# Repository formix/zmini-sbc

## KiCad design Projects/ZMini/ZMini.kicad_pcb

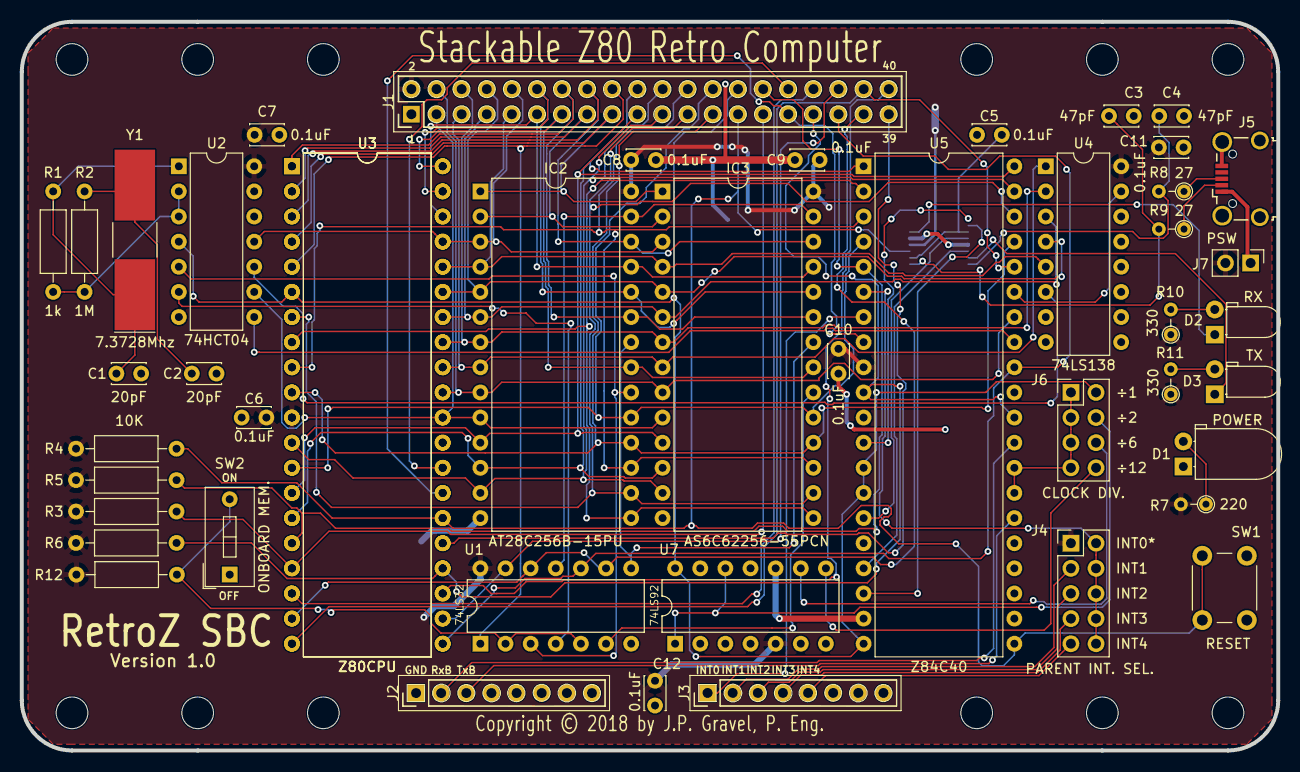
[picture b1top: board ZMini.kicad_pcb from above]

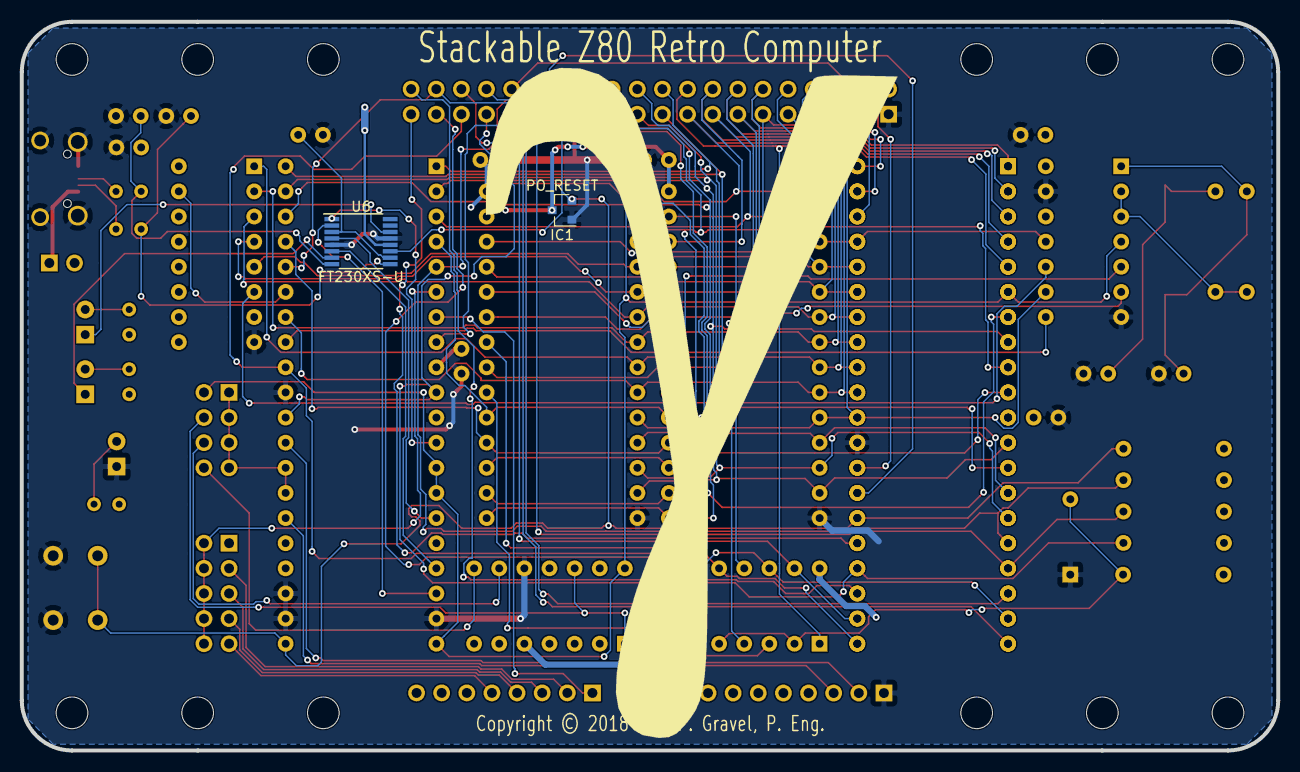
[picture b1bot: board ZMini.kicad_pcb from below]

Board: 2 copper layers, 127.0 x 73.7 mm, 60 parts (2 on the bottom side), 79 nets.

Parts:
C1, C2: 20pF; C_Disc_D3.4mm_W2.1mm_P2.50mm
C3, C4: 47pF; C_Disc_D3.4mm_W2.1mm_P2.50mm
C5, C6, C7, C8, C9, C10, C11, C12: 0.1uF; C_Disc_D3.4mm_W2.1mm_P2.50mm
D1: POWER; LED_D5.0mm_Horizontal_O1.27mm_Z3.0mm
D2: RX; LED_D3.0mm_Horizontal_O1.27mm_Z2.0mm
D3: TX; LED_D3.0mm_Horizontal_O1.27mm_Z2.0mm
H1, H2, H3, H4, H5, H6, H7, H8, H9, H10, H11, H12: MountingHole; MountingHole_3.2mm_M3
IC1: PO_RESET; SOT-23
IC2: AT28C256B-15PU; DIP-28_W15.24mm
IC3: AS6C62256-55PCN; DIP-28_W15.24mm
J1: 02x20; Pin_Header_Straight_2x20_Pitch2.54mm
J2, J3: 01x08; Socket_Strip_Straight_1x08_Pitch2.54mm
J4: PARENT INT. SEL.; Pin_Header_Straight_2x05_Pitch2.54mm
J5: USB_OTG; USB_Micro-B_Wuerth-629105150521_CircularHoles
J6: CLOCK DIV.; Pin_Header_Straight_2x04_Pitch2.54mm
J7: PSW; Pin_Header_Straight_1x02_Pitch2.54mm
R1: 1M; R_Axial_DIN0207_L6.3mm_D2.5mm_P10.16mm_Horizontal
R2: 1k; R_Axial_DIN0207_L6.3mm_D2.5mm_P10.16mm_Horizontal
R3, R4, R5, R6, R12: 10K; R_Axial_DIN0207_L6.3mm_D2.5mm_P10.16mm_Horizontal
R7: 220; R_Axial_DIN0204_L3.6mm_D1.6mm_P2.54mm_Vertical
R8, R9: 27; R_Axial_DIN0204_L3.6mm_D1.6mm_P2.54mm_Vertical
R10, R11: 330; R_Axial_DIN0204_L3.6mm_D1.6mm_P2.54mm_Vertical
SW1: RESET; SW_PUSH_6mm_h5mm
SW2: ONBOARD MEM.; SW_DIP_x1_W7.62mm_Slide
U1: 74LS32; DIP-14_W7.62mm
U2: 74HCT04; DIP-14_W7.62mm
U3, U3#2: Z80CPU; DIP-40_W15.24mm
U4: 74LS138; DIP-16_W7.62mm
U5: Z84C40; DIP-40_W15.24mm
U6: FT230XS-U; TSSOP-16_4.4x5mm_Pitch0.65mm
U7: 74LS92; DIP-14_W7.62mm
Y1: 7.3728Mhz; Crystal_SMD_SeikoEpson_MC405-2pin_9.6x4.1mm_HandSoldering

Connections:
/A0: IC2.10, IC3.10, J1.3, U2.9, U3.30, U3#2.30
/A1: IC2.9, IC3.9, J1.4, U3.31, U3#2.31, U5.34
/A2: IC2.8, IC3.8, J1.5, U3.32, U3#2.32, U4.1
/A3: IC2.7, IC3.7, J1.6, U3.33, U3#2.33, U4.2
/A4: IC2.6, IC3.6, J1.7, U3.34, U3#2.34, U4.3
/A5: IC2.5, IC3.5, J1.8, U3.35, U3#2.35, U4.4
/A6: IC2.4, IC3.4, J1.9, U3.36, U3#2.36, U4.5
/A7: IC2.3, IC3.3, J1.10, U2.11, U3.37, U3#2.37
/A8: IC2.25, IC3.25, J1.11, U3.38, U3#2.38
/A9: IC2.24, IC3.24, J1.12, U3.39, U3#2.39
/A10: IC2.21, IC3.21, J1.13, U3.40, U3#2.40
/A11: IC2.23, IC3.23, J1.14, U3.1, U3#2.1
/A12: IC2.2, IC3.2, J1.15, U3.2, U3#2.2
/A13: IC2.26, IC3.26, J1.16, U3.3, U3#2.3
/A14: IC2.1, IC3.1, J1.17, U3.4, U3#2.4
/A15: J1.18, U1.1, U3.5, U3#2.5
/CLK_01: J6.4, U7.1, U7.12
/CLK_02: J6.6, U7.9
/CLK_03: J6.8, U7.8
/D0: IC2.11, IC3.11, J1.19, U3.14, U3#2.14, U5.40
/D1: IC2.12, IC3.12, J1.20, U3.15, U3#2.15, U5.1
/D2: IC2.13, IC3.13, J1.21, U3.12, U3#2.12, U5.39
/D3: IC2.15, IC3.15, J1.22, U3.8, U3#2.8, U5.2
/D4: IC2.16, IC3.16, J1.23, U3.7, U3#2.7, U5.38
/D5: IC2.17, IC3.17, J1.24, U3.9, U3#2.9, U5.3
/D6: IC2.18, IC3.18, J1.25, U3.10, U3#2.10, U5.37
/D7: IC2.19, IC3.19, J1.26, U3.13, U3#2.13, U5.4
/IEI: J4.2, J4.4, J4.6, J4.8, J4.10, U5.6
/INT_0: J3.1, U5.7
/INT_1: J3.2, J4.3
/INT_2: J3.3, J4.5
/INT_3: J3.4, J4.7
/INT_4: J3.5, J4.9
/ONB_MEM: R12.1, SW2.2, U1.2, U1.5
/RAM_SEL: IC3.20, U1.6
/ROM_SEL: IC2.20, U1.3, U2.5
/Rx: U5.15, U6.4
/RxB: J2.2, U5.29
/SIO2_SEL: U4.15, U5.35
/SIOB_CLK: J6.1, J6.3, J6.5, J6.7, U5.27, U5.28
/Tx: U5.12, U6.1
/TxB: J2.3, U5.26
/~BUSACK: J1.40, U3.23, U3#2.23
/~BUSRQ: J1.39, U3.25, U3#2.25
/~CLK: J1.28, J6.2, U2.4, U3.6, U3#2.6, U5.13, U5.14, U5.20, U7.14
/~CTS: U5.17, U6.6
/~HALT: J1.34, U3.18, U3#2.18
/~INT: J1.30, R5.2, U3.16, U3#2.16, U5.5
/~IORQ: J1.38, U3.20, U3#2.20, U5.36
/~M1: J1.31, U3.27, U3#2.27, U5.8
/~MRD: IC2.22, IC3.22, U1.8
/~MREQ: J1.37, U1.9, U1.12, U3.19, U3#2.19
/~MWR: IC2.27, IC3.27, U1.11
/~NMI: J1.29, R3.2, U3.17, U3#2.17
/~RD: J1.35, U1.10, U3.21, U3#2.21, U5.32
/~RESET: IC1.2, J1.27, R4.2, SW1.2, U3.26, U3#2.26, U5.21, U6.11
/~RFSH: J1.32, U3.28, U3#2.28
/~RTS: U5.18, U6.2
/~WAIT: J1.33, R6.2, U3.24, U3#2.24, U5.10, U5.30
/~WR: J1.36, U1.13, U3.22, U3#2.22
GND: C1.2, C2.2, C3.2, C4.2, C5.2, C6.2, C7.2, C8.2, C9.2, C10.2, C11.2, C12.2, D1.1, IC1.1, IC2.14, IC3.14, J1.1, J2.1, J5.5, J5.6, SW1.1, SW2.1, U1.7, U2.7, U2.13, U3.29, U3#2.29, U4.8, U5.19, U5.22, U5.23, U5.31, U6.5, U6.13, U7.10
unnamed: C1.1, R1.2, U2.1, Y1.1
unnamed: C2.1, R2.1, Y1.2
unnamed: C3.1, R9.2, U6.9
unnamed: C4.1, R8.2, U6.8
unnamed: C5.1, U6.3, U6.10
unnamed: D1.2, R7.1
unnamed: D2.1, U6.14
unnamed: D2.2, R10.2
unnamed: D3.1, U6.7
unnamed: D3.2, R11.2
unnamed: J5.1, J7.1
unnamed: J5.2, R9.1
unnamed: J5.3, R8.1
unnamed: R1.1, R2.2, U2.2, U2.3
unnamed: U1.4, U2.6
unnamed: U2.8, U5.33
unnamed: U2.10, U4.6
VCC: C6.1, C7.1, C8.1, C9.1, C10.1, C11.1, C12.1, IC1.3, IC2.28, IC3.28, J1.2, J4.1, J7.2, R3.1, R4.1, R5.1, R6.1, R7.2, R10.1, R11.1, R12.2, U1.14, U2.14, U3.11, U3#2.11, U4.16, U5.9, U6.12, U7.5

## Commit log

2018-12-31 added a memory selector and other stuff
2018-12-31 added the memory board sense

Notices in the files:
Projects/ZMini/ZMini.kicad_pcb:
Copyright (c) 2018 by J.P. Gravel, P. eng.
Copyright © 2018 by J.P. Gravel, P. Eng.
